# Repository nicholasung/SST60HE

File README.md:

# SST60

## Changes
Added Hall effects under WASD for Gateron KS20
Removed the Hotswap diredctory as the solder is to keep consistent pcb and switch spacing

PCB is on rev 0.1 (theoretically ready but untested)

# Recommended Builds

### Budget $96 CAD Before PCB & Magnetics
  [Case $15](https://www.amazon.ca/Dciustfhe-Plastic-Mechanical-Keyboard-Shell/dp/B0BJPQZM5W/?_encoding=UTF8&pd_rd_w=fi4cm&content-id=amzn1.sym.2fd36d35-e0d1-4258-ba0c-e42eba5f6561%3Aamzn1.symc.e5c80209-769f-4ade-a325-2eaec14b8e0e&pf_rd_p=2fd36d35-e0d1-4258-ba0c-e42eba5f6561&pf_rd_r=AD63PT5KJBTNQTJFS9E1&pd_rd_wg=ocsUf&pd_rd_r=7f42a560-1041-47c4-9e6a-61577ff59043&ref_=pd_gw_ci_mcx_mr_hp_atf_m), 
  [Switches $35](https://www.amazon.ca/Switch-Linear-Customization-Mechanical-Keyboard/dp/B0BQJ2Y3RX/ref=sr_1_15?crid=2727HL4GOP4JB&keywords=mx%2Bswitches&qid=1699499585&sprefix=mx%2Bswitches%2Caps%2C142&sr=8-15&th=1), 
  [Plate $20](https://www.amazon.ca/stabilizers-Universal-Anodized-Aluminum-Positioning/dp/B06W2L4MCT/ref=sr_1_4?crid=1E5UX13UMMICS&keywords=60%25+plate&qid=1699499699&sprefix=60%25+pla%2Caps%2C139&sr=8-4), 
  [Stabilizers $26](https://www.amazon.ca/DUROCK-Stabilizers-Translucent-Mechanical-Keyboard/dp/B08MWDGBJ8/ref=sr_1_13?crid=2L2ZT84DR52J0&keywords=keyboard%2Bstabilizers&qid=1699499779&sprefix=keyboardstabilizers%2Caps%2C119&sr=8-13&th=1), 
  This PCB, and 4x Gateron KS20s or Wooting Lekker Switches  

### Premium (My Personal Setup) ~$185 Before PCB & Magnetics
[Case, Plate, Stabs, $135](https://cannonkeys.com/products/bakeneko-60)
[Switches $35](https://www.aliexpress.com/item/1005004557654365.html?spm=a2g0o.productlist.main.1.6599f9ceqvZntK&algo_pvid=a1e5913e-a6d8-4189-a002-4bd6378e958d&algo_exp_id=a1e5913e-a6d8-4189-a002-4bd6378e958d-0&pdp_npi=4%40dis%21CAD%2139.69%2139.69%21%21%2128.14%21%21%402101e9a216995000223577681effc2%2112000034147033012%21sea%21CA%211612292949%21&curPageLogUid=2eWo8CgdRKUC)

## Fully open source multi-layout 60% PCB

<sub> renders outdated, using the old outline. </sub>

## Layout support

## Features
- RGB Underglow
- RP2040 processor
- MX and Alps compatible
- Indicator light positions for Caps Lock and Esc
- Standard tray mount support
- Gummy O-Ring support (Bakenko, ogre, etc. anything that h60 supports, this does too.)
- USB-C or Unified Daughterboard (or equivalent with the same pinout)
- Overcurrent and ESD protection
- Flex meme cuts

## ***DISCLAIMER***
This PCB has been tested and confirmed to work properly. The members of the PCB development team are not liable if you end up with a non-functional pcb. Order at your own risk. Support will not be provided but pull requests will be reviewed and possibly accepted.

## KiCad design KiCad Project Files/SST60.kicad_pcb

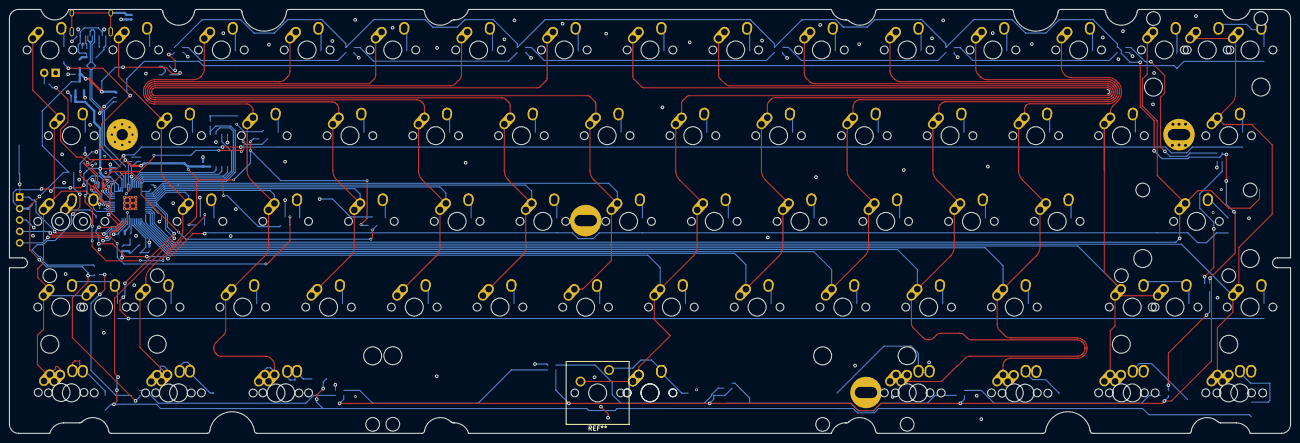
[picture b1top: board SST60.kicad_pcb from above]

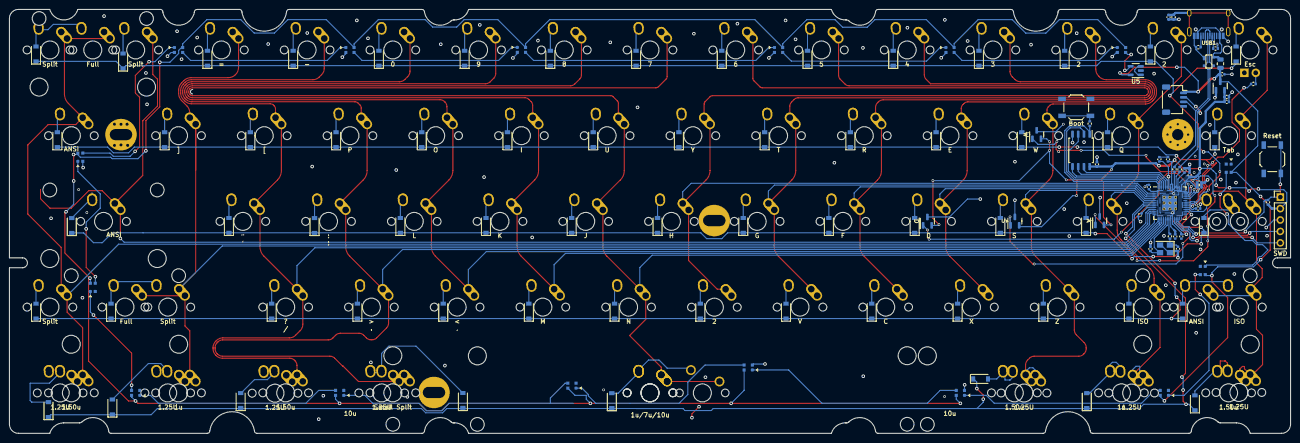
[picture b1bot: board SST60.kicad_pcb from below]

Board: 2 copper layers, 284.7 x 94.2 mm, 200 parts (123 on the bottom side), 132 nets.

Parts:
0, 1u, 1u#2, 1u/7u/10u, 2, 2#2, 2#3, 3, 4, 5, 6, 7, 8, 9: MX-NoLED; MX-1U-NoLED
1.25U, 1.25U#2, 1.25U#3, 1.25U#4, 1.25U#5, 1.25U#6, 1.25U#7: MX-NoLED; MX-1.25U-NoLED
1.50u, 1.50u#2, 1.50u#3, 1.50u#4: MX-NoLED; MX-1.5U-NoLED
": '; MX-1U-NoLED
-: MX-NoLED; MX-1U-NoLED
:: ;; MX-1U-NoLED
<: ,; MX-1U-NoLED
=: MX-NoLED; MX-1U-NoLED
>: .; MX-1U-NoLED
?: /; MX-1U-NoLED
A: MX-NoLED; MX-1U-NoLED
A#2: SOT-23
ANSI: MX-NoLED; MX-2.25U-NoLED
ANSI#2: MX-NoLED; MX-1.5U-NoLED
ANSI#3: MX-NoLED; MX-2.25U-NoLED
C: MX-NoLED; MX-1U-NoLED
C_1V-Decoup1, C_3V-Decoup2: 1u; C_0402_1005Metric
C_1V-Decoup2, C_1V-Decoup3, C_3V-Decoup3, C_3V-Decoup4, C_3V-Decoup5, C_3V-Decoup6, C_3V-Decoup7, C_3V-Decoup8, C_3V-Decoup9: .1u; C_0402_1005Metric
C_3V-Decoup1: 10u; C_0402_1005Metric
C_Crystal1, C_Crystal2: 22pF; C_0402_1005Metric
C_Flash1: .1u; C_0402_1005Metric
C_LDO1, C_LDO2: 1u; C_0402_1005Metric
C_Shield1: 4.7n; C_0402_1005Metric
D: MX-NoLED; MX-1U-NoLED
D1, D2, D3, D4, D5, D6, D7, D8, D9, D10, D11, D12, D13, D14, D15, D16, D17, D18, D19, D20, D21, D22, D23, D25, D26, D27, D28, D30, D31, D32, D33, D34, D35, D36, D37, D38, D39, D40, D41, D42, D43, D44, D45, D46, D48, D49, D50, D51, D52, D53, D54, D55, D56, D57, D58, D59, D61, D62, D63, D64, D65, D66, D67, D68: D_Small; D_SOD-123
D69, D70, D71, D72, D73, D74, D75, D76, D77, D78, D79, D80, D81, D82, D83, D84: WS2812B-2020; LED_WS2812_2020
D#2: SOT-23
E: MX-NoLED; MX-1U-NoLED
Esc: MX-LED; MX-1U
F: MX-NoLED; MX-1U-NoLED
F1: 500mA; Fuse_0805_2012Metric
Full: MX-NoLED; MX-2.75U-NoLED
Full#2: MX-NoLED; MX-2U-NoLED
Full#3: MX-LED; MX-1.75U
G: MX-NoLED; MX-1U-NoLED
H: MX-NoLED; MX-1U-NoLED
H1: PCB Outline; L60 Outline
I: MX-NoLED; MX-1U-NoLED
ISO: MX-NoLED; MX-1U-NoLED
ISO#2: MX-NoLED; MX-1.25U-NoLED
J: MX-NoLED; MX-1U-NoLED
J1: SM04B; JST_SH_SM04B-SRSS-TB_1x04-1MP_P1.00mm_Horizontal
J2: SWD; PinHeader_1x05_P2.54mm_Vertical
K: MX-NoLED; MX-1U-NoLED
L: MX-NoLED; MX-1U-NoLED
M: MX-NoLED; MX-1U-NoLED
MX42: MX-NoLED; MX-7U-ReversedStabilizers-NoLED
N: MX-NoLED; MX-1U-NoLED
O: MX-NoLED; MX-1U-NoLED
P: MX-NoLED; MX-1U-NoLED
Q: MX-NoLED; MX-1U-NoLED
R: MX-NoLED; MX-1U-NoLED
R_Crystal1: 1k; R_0402_1005Metric
R_DATA1, R_DATA2: 27; R_0402_1005Metric
R_Flash1: 1k; R_0402_1005Metric
R_LED1: 220; R_0402_1005Metric
R_RST1: 1k; R_0402_1005Metric
R_Shield1: 1M; R_0402_1005Metric
R_USB1, R_USB2: 5k1; R_0402_1005Metric
S: MX-NoLED; MX-1U-NoLED
S#2: SOT-23
SW1: Boot; SW_SPST_TL3342
SW2: Reset; SW_SPST_TL3342
Small Split: MX-NoLED; MX-1U-NoLED
Split: MX-NoLED; MX-1U-NoLED
Split#2: MX-NoLED; MX-1.75U-NoLED
Split#3, Split#4: MX-NoLED; MX-1U-NoLED
Stepped: MX-LED; MX-1.25U-FLIPPED
T: MX-NoLED; MX-1U-NoLED
Tab: MX-NoLED; MX-1.5U-NoLED
U: MX-NoLED; MX-1U-NoLED
U1: RP2040; RP2040-QFN-56
U2: W25Q128JVS; SOIC-8_5.23x5.23mm_P1.27mm
U3: XC6206PxxxMR; SOT-23
U4: PRTR5V0U2X; SOT143B
U5: 74AHCT1G125; SOT-23-5
USB1: HRO-TYPE-C-31-M-12; HRO-TYPE-C-31-M-12-Assembly
V: MX-NoLED; MX-1U-NoLED
W: MX-NoLED; MX-1U-NoLED
W#2: SOT-23
X: MX-NoLED; MX-1U-NoLED
Y: MX-NoLED; MX-1U-NoLED
Y1: 12MHz; Crystal_SMD_3225-4Pin_3.2x2.5mm
Z: MX-NoLED; MX-1U-NoLED
[: MX-NoLED; MX-1U-NoLED
]: MX-NoLED; MX-1U-NoLED

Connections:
+1V1: C_1V-Decoup1.1, C_1V-Decoup2.1, C_1V-Decoup3.1, U1.23 (DVDD), U1.45 (VREG_VOUT), U1.50 (DVDD)
+3V3: A#2.VDD, C_3V-Decoup1.1, C_3V-Decoup2.1, C_3V-Decoup3.1, C_3V-Decoup4.1, C_3V-Decoup5.1, C_3V-Decoup6.1, C_3V-Decoup7.1, C_3V-Decoup8.1, C_3V-Decoup9.1, C_Flash1.1, C_LDO2.1, D#2.VDD, J2.2, R_RST1.1, S#2.VDD, U1.1 (IOVDD), U1.10 (IOVDD), U1.22 (IOVDD), U1.33 (IOVDD), U1.42 (IOVDD), U1.43 (ADC_AVDD), U1.44 (VREG_VIN), U1.48 (USB_VDD), U1.49 (IOVDD), U2.8 (VCC), U3.2 (VO), W#2.VDD
+5V: C_LDO1.1, D69.4 (VDD), D70.4 (VDD), D71.4 (VDD), D72.4 (VDD), D73.4 (VDD), D74.4 (VDD), D75.4 (VDD), D76.4 (VDD), D77.4 (VDD), D78.4 (VDD), D79.4 (VDD), D80.4 (VDD), D81.4 (VDD), D82.4 (VDD), D83.4 (VDD), D84.4 (VDD), F1.2, J1.1, U3.3 (VI), U5.5 (+5V)
A: A#2.A, U1.39 (GPIO27/ADC1)
CS: R_Flash1.2, U1.56 (QSPI_SS_N), U2.1 (~CS)
D: D#2.D, U1.41 (GPIO29/ADC3)
D+: J1.3, R_DATA1.1, U4.2 (IO1), USB1.6 (DP1), USB1.8 (DP2)
D-: J1.2, R_DATA2.1, U4.3 (IO2), USB1.5 (DN2), USB1.7 (DN1)
ESCLED: R_LED1.1, U1.34 (GPIO22)
GND: A#2.GND, C_1V-Decoup1.2, C_1V-Decoup2.2, C_1V-Decoup3.2, C_3V-Decoup1.2, C_3V-Decoup2.2, C_3V-Decoup3.2, C_3V-Decoup4.2, C_3V-Decoup5.2, C_3V-Decoup6.2, C_3V-Decoup7.2, C_3V-Decoup8.2, C_3V-Decoup9.2, C_Crystal1.1, C_Crystal2.1, C_Flash1.2, C_LDO1.2, C_LDO2.2, C_Shield1.1, D69.2 (VSS), D70.2 (VSS), D71.2 (VSS), D72.2 (VSS), D73.2 (VSS), D74.2 (VSS), D75.2 (VSS), D76.2 (VSS), D77.2 (VSS), D78.2 (VSS), D79.2 (VSS), D80.2 (VSS), D81.2 (VSS), D82.2 (VSS), D83.2 (VSS), D84.2 (VSS), D#2.GND, Esc.4 (LEDGND), H1.1, J1.4, J2.3, R_Shield1.2, R_USB1.2, R_USB2.2, S#2.GND, SW1.1, SW2.2, U1.19 (TESTEN), U1.57 (GND), U2.4 (GND), U3.1 (GND), U4.1 (GND), U5.1, U5.3 (GND), USB1.1 (GND), USB1.12 (GND), W#2.GND, Y1.2, Y1.4
GNDREF: C_Shield1.2, R_Shield1.1, USB1.13 (SHIELD)
unnamed: C_Crystal2.2, R_Crystal1.1, Y1.1
unnamed: D1.2 (A), Esc.2 (ROW)
unnamed: D2.2 (A), Tab.2 (ROW)
unnamed: D3.2 (A), Full#3.1 (ROW), Stepped.2 (ROW)
unnamed: ANSI#3.2 (ROW), D4.2 (A), ISO#2.2 (ROW)
unnamed: 1.25U#6.2 (ROW), 1.50u.2 (ROW), D5.2 (A)
unnamed: 2.2 (ROW), D6.2 (A)
unnamed: D7.2 (A), Q.2 (ROW)
unnamed: A.2 (ROW), D8.2 (A)
unnamed: D9.2 (A), ISO.2 (ROW)
unnamed: 1.25U.2 (ROW), 1u#2.2 (ROW), D10.2 (A)
unnamed: D11.2 (A), Z.2 (ROW)
unnamed: 2#3.2 (ROW), D12.2 (A)
unnamed: D13.2 (A), W.2 (ROW)
unnamed: D14.2 (A), S.2 (ROW)
unnamed: 1.25U#2.2 (ROW), 1.50u#3.2 (ROW), D15.2 (A)
unnamed: 3.2 (ROW), D16.2 (A)
unnamed: D17.2 (A), E.2 (ROW)
unnamed: D.2 (ROW), D18.2 (A)
unnamed: D19.2 (A), X.2 (ROW)
unnamed: 4.2 (ROW), D20.2 (A)
unnamed: D21.2 (A), R.2 (ROW)
unnamed: D22.2 (A), F.2 (ROW)
unnamed: C.2 (ROW), D23.2 (A)
unnamed: 5.2 (ROW), D25.2 (A)
unnamed: D26.2 (A), T.2 (ROW)
unnamed: D27.2 (A), G.2 (ROW)
unnamed: D28.2 (A), V.2 (ROW)
unnamed: 6.2 (ROW), D30.2 (A)
unnamed: D31.2 (A), Y.2 (ROW)
unnamed: D32.2 (A), H.2 (ROW)
unnamed: 2#2.2 (ROW), D33.2 (A)
unnamed: 7.2 (ROW), D34.2 (A)
unnamed: D35.2 (A), U.2 (ROW)
unnamed: D36.2 (A), J.2 (ROW)
unnamed: D37.2 (A), N.2 (ROW)
unnamed: 1u/7u/10u.2 (ROW), D38.2 (A), MX42.2 (ROW)
unnamed: 8.2 (ROW), D39.2 (A)
unnamed: D40.2 (A), I.2 (ROW)
unnamed: D41.2 (A), K.2 (ROW)
unnamed: D42.2 (A), M.2 (ROW)
unnamed: 9.2 (ROW), D43.2 (A)
unnamed: D44.2 (A), O.2 (ROW)
unnamed: D45.2 (A), L.2 (ROW)
unnamed: <.2 (ROW), D46.2 (A)
unnamed: 0.2 (ROW), D48.2 (A)
unnamed: D49.2 (A), P.2 (ROW)
unnamed: :.2 (ROW), D50.2 (A)
unnamed: >.2 (ROW), D51.2 (A)
unnamed: 1.25U#3.2 (ROW), 1.25U#3.d52 (ROW), D52.2 (A), Small Split.2 (ROW)
unnamed: -.2 (ROW), D53.2 (A)
unnamed: D54.2 (A), [.2 (ROW)
unnamed: ".2 (ROW), D55.2 (A)
unnamed: ?.2 (ROW), D56.2 (A)
unnamed: 1.25U#7.2 (ROW), 1.50u#2.2 (ROW), D57.2 (A)
unnamed: =.2 (ROW), D58.2 (A)
unnamed: D59.2 (A), ].2 (ROW)
unnamed: D61.2 (A), Full.2 (ROW), Split#2.2 (ROW)
unnamed: 1.25U#5.2 (ROW), 1u.2 (ROW), D62.2 (A)
unnamed: D63.2 (A), Split#4.2 (ROW)
unnamed: ANSI.2 (ROW), D64.2 (A)
unnamed: D65.2 (A), Full#2.2 (ROW), Split#3.2 (ROW)
unnamed: ANSI#2.2 (ROW), D66.2 (A)
unnamed: D67.2 (A), Split.2 (ROW)
unnamed: 1.25U#4.2 (ROW), 1.50u#4.2 (ROW), D68.2 (A)
unnamed: D69.3 (DIN), D70.1 (DOUT)
unnamed: D70.3 (DIN), D72.1 (DOUT)
unnamed: D71.1 (DOUT), D73.3 (DIN)
unnamed: D72.3 (DIN), D74.1 (DOUT)
unnamed: D73.1 (DOUT), D75.3 (DIN)
unnamed: D74.3 (DIN), D76.1 (DOUT)
unnamed: D75.1 (DOUT), D77.3 (DIN)
unnamed: D76.3 (DIN), D78.1 (DOUT)
unnamed: D77.1 (DOUT), D79.3 (DIN)
unnamed: D78.3 (DIN), D80.1 (DOUT)
unnamed: D79.1 (DOUT), D81.3 (DIN)
unnamed: D80.3 (DIN), D82.1 (DOUT)
unnamed: D81.1 (DOUT), D83.3 (DIN)
unnamed: D82.3 (DIN), D84.1 (DOUT)
unnamed: D83.1 (DOUT), D84.3 (DIN)
unnamed: Esc.3 (LED), R_LED1.2
unnamed: R_DATA1.2, U1.47 (D+)
unnamed: R_DATA2.2, U1.46 (D-)
unnamed: R_Flash1.1, SW1.2
unnamed: R_USB1.1, USB1.4 (CC1)
unnamed: R_USB2.1, USB1.10 (CC2)
QSPI_CLK: U1.52 (QSPI_SCLK), U2.6 (CLK)
RESET: J2.1, R_RST1.2, SW2.1, U1.26 (~RUN)
RGB: D71.3 (DIN), U5.4
RGBLED: U1.37 (GPIO25), U5.2
S: S#2.S, U1.40 (GPIO28/ADC2)
SD0: U1.53 (QSPI_SD0), U2.5 (DI(IO0))
SD1: U1.55 (QSPI_SD1), U2.2 (DO(IO1))
SD2: U1.54 (QSPI_SD2), U2.3 (IO2)
SD3: U1.51 (QSPI_SD3), U2.7 (IO3)
SWCLK: J2.5, U1.24 (SWCLK)
SWDIO: J2.4, U1.25 (SWDIO)
VCC: F1.1, U4.4 (VCC), USB1.2 (VBUS), USB1.11 (VBUS)
W: U1.38 (GPIO26/ADC0), W#2.W
XTAL_IN: C_Crystal1.2, U1.20 (XTAL_IN), Y1.3
XTAL_OUT: R_Crystal1.2, U1.21 (XTAL_OUT)
col0: 1.25U#6.1 (COL), 1.50u.1 (COL), ANSI#3.1 (COL), Esc.1 (COL), Full#3.2 (COL), ISO#2.1 (COL), Stepped.1 (COL), Tab.1 (COL), U1.32 (GPIO21)
col1: 1.25U.1 (COL), 1u#2.1 (COL), 2.1 (COL), A.1 (COL), ISO.1 (COL), Q.1 (COL), U1.7 (GPIO5)
col2: 1.25U#2.1 (COL), 1.50u#3.1 (COL), 2#3.1 (COL), S.1 (COL), U1.6 (GPIO4), W.1 (COL), Z.1 (COL)
col3: 3.1 (COL), D.1 (COL), E.1 (COL), U1.5 (GPIO3), X.1 (COL)
col4: 4.1 (COL), C.1 (COL), F.1 (COL), R.1 (COL), U1.4 (GPIO2)
col5: 5.1 (COL), G.1 (COL), T.1 (COL), U1.3 (GPIO1), V.1 (COL)
col6: 2#2.1 (COL), 6.1 (COL), H.1 (COL), U1.2 (GPIO0), Y.1 (COL)
col7: 1u/7u/10u.1 (COL), 7.1 (COL), J.1 (COL), MX42.1 (COL), N.1 (COL), U.1 (COL), U1.18 (GPIO15)
col8: 8.1 (COL), I.1 (COL), K.1 (COL), M.1 (COL), U1.17 (GPIO14)
col9: 9.1 (COL), <.1 (COL), L.1 (COL), O.1 (COL), U1.16 (GPIO13)
col10: 0.1 (COL), 1.25U#3.1 (COL), :.1 (COL), >.1 (COL), P.1 (COL), Small Split.1 (COL), U1.15 (GPIO12)
col11: 1.25U#7.1 (COL), 1.50u#2.1 (COL), ".1 (COL), -.1 (COL), ?.1 (COL), U1.14 (GPIO11), [.1 (COL)
col12: 1.25U#5.1 (COL), 1u.1 (COL), =.1 (COL), Full.1 (COL), Split#2.1 (COL), U1.13 (GPIO10), ].1 (COL)
col13: ANSI.1 (COL), Split#4.1 (COL), U1.11 (GPIO8)
col14: 1.25U#4.1 (COL), 1.50u#4.1 (COL), ANSI#2.1 (COL), Full#2.1 (COL), Split.1 (COL), Split#3.1 (COL), U1.12 (GPIO9)
row0: D1.1 (K), D6.1 (K), D12.1 (K), D16.1 (K), D20.1 (K), D25.1 (K), D30.1 (K), D34.1 (K), D39.1 (K), D43.1 (K), D48.1 (K), D53.1 (K), D58.1 (K), D63.1 (K), D65.1 (K), U1.36 (GPIO24)
row1: D2.1 (K), D7.1 (K), D13.1 (K), D17.1 (K), D21.1 (K), D26.1 (K), D31.1 (K), D35.1 (K), D40.1 (K), D44.1 (K), D49.1 (K), D54.1 (K), D59.1 (K), D66.1 (K), U1.35 (GPIO23)
row2: D3.1 (K), D8.1 (K), D14.1 (K), D18.1 (K), D22.1 (K), D27.1 (K), D32.1 (K), D36.1 (K), D41.1 (K), D45.1 (K), D50.1 (K), D55.1 (K), D64.1 (K), U1.31 (GPIO20)
row3: D4.1 (K), D9.1 (K), D11.1 (K), D19.1 (K), D23.1 (K), D28.1 (K), D33.1 (K), D37.1 (K), D42.1 (K), D46.1 (K), D51.1 (K), D56.1 (K), D61.1 (K), D67.1 (K), U1.8 (GPIO6)
row4: D5.1 (K), D10.1 (K), D15.1 (K), D38.1 (K), D52.1 (K), D57.1 (K), D62.1 (K), D68.1 (K), U1.9 (GPIO7)

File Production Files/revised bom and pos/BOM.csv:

Comment,Designator,Footprint,LCSC
1k,"R_Crystal1,R_Flash1,R_RST1",R_0402_1005Metric,C11702
PRTR5V0U2X,U4,SOT143B,C12333
.1u,"C_1V-Decoup2,C_1V-Decoup3,C_3V-Decoup3,C_3V-Decoup4,C_3V-Decoup5,C_3V-Decoup6,C_3V-Decoup7,C_3V-Decoup8,C_3V-Decoup9,C_Flash1",C_0402_1005Metric,C1525
4.7n,C_Shield1,C_0402_1005Metric,C1538
10u,C_3V-Decoup1,C_0402_1005Metric,C15525
22pF,"C_Crystal1,C_Crystal2",C_0402_1005Metric,C1555
HRO-TYPE-C-31-M-12,USB1,HRO-TYPE-C-31-M-12-Assembly,C165948
RP2040,U1,RP2040-QFN-56,C2040
220,"R_LED1,R_LED2",R_0402_1005Metric,C25091
27,"R_DATA1,R_DATA2",R_0402_1005Metric,C25100
5k1,"R_USB1,R_USB2",R_0402_1005Metric,C25905
1M,R_Shield1,R_0402_1005Metric,C26083
Boot,"SW1,SW2",SW_SPST_TL3342,C318884
1u,"C_1V-Decoup1,C_3V-Decoup2,C_LDO1,C_LDO2",C_0402_1005Metric,C52923
XC6206PxxxMR,U3,SOT-23,C5446
D_Small,"D1,D10,D11,D12,D13,D14,D15,D16,D17,D18,D19,D2,D20,D21,D22,D23,D24,D25,D26,D27,D28,D29,D3,D30,D31,D32,D33,D34,D35,D36,D37,D38,D39,D4,D40,D41,D42,D43,D44,D45,D46,D47,D48,D49,D5,D50,D51,D52,D53,D54,D55,D56,D57,D58,D59,D6,D60,D61,D62,D63,D64,D65,D66,D67,D68,D7,D8,D9",D_SOD-123,C64898
74AHCT1G125,U5,SOT-23-5,C7468
500mA,F1,Fuse_0805_2012Metric,C883103
12MHz,Y1,Crystal_SMD_3225-4Pin_3.2x2.5mm,C9002
WS2812B-2020,"D69,D70,D71,D72,D73,D74,D75,D76,D77,D78,D79,D80,D81,D82,D83,D84",LED_WS2812_2020,C965555
W25Q128JVS,U2,SOIC-8_5.23x5.23mm_P1.27mm,C97521
SM04B,J1,JST_SH_SM04B-SRSS-TB_1x04-1MP_P1.00mm_Horizontal,C145956
Hall Sensor,"W,A,S,D",SOT-23,C2904393

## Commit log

2023-11-08 Add files via upload
    updated schematics
2023-11-09 Wired up the hall effects, removed some led traces and the flex cuts
2023-11-09 Added FR4 Plate files
    Based on GH60 and Bakeneko plates
2023-11-09 Reworked Bottom Row
    Now only supports ansi and tsangan sacrificing flexibility for simplicity and wider standards.
2023-11-09 Cleaned Traces
    Updated traces, generated new gerber, pos and bom, removed iso enter support
2023-11-09 fixed missing trace
2023-11-09 added traces for "c" and "1"
2023-11-10 BOM and POS files added
    Both JST and USB are installed on default.
2023-11-10 cleaned up dirs
2023-11-10 BOM and POS are fully matching pcb
